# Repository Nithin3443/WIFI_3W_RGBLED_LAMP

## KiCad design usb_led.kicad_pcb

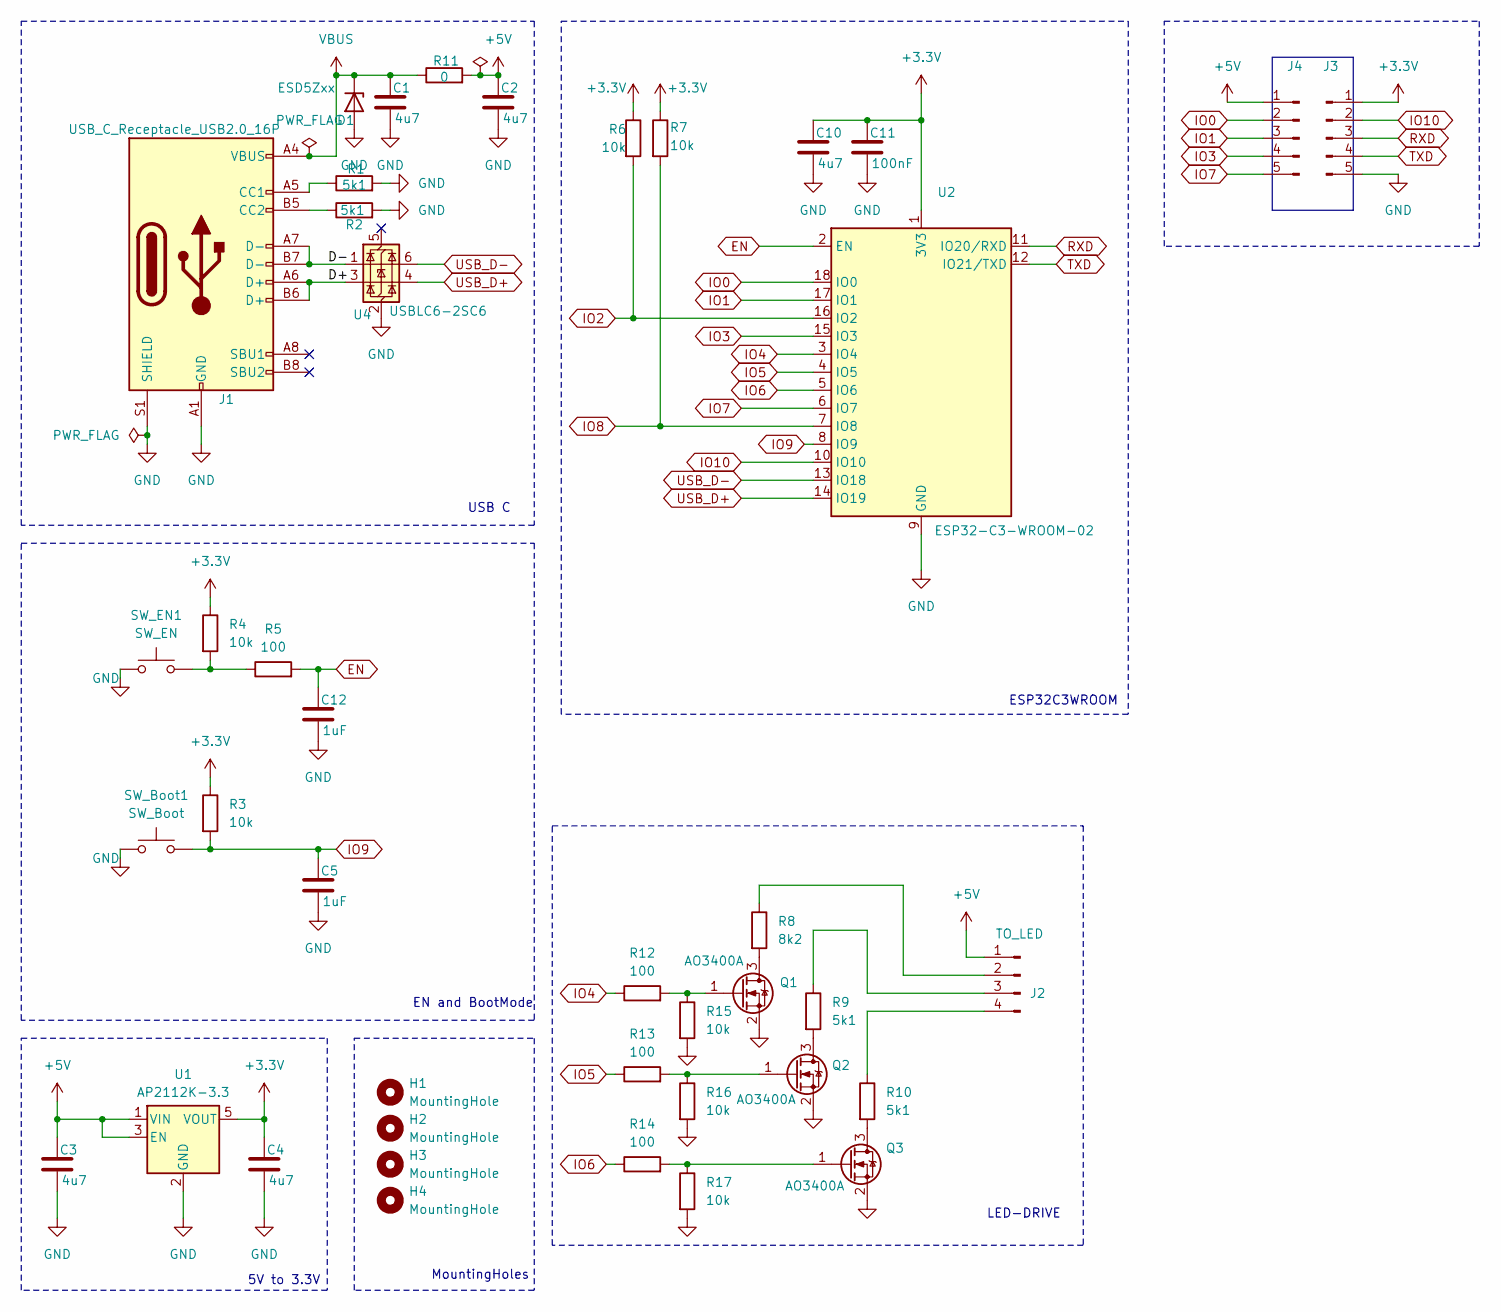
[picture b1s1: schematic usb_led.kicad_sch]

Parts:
C1, C3, C4, C10: 4u7; C_1206_3216Metric_Pad1.33x1.80mm_HandSolder
C2: 4u7; C_0805_2012Metric_Pad1.18x1.45mm_HandSolder
C5, C12: 1uF; C_0805_2012Metric_Pad1.18x1.45mm_HandSolder
C11: 100nF; C_0805_2012Metric_Pad1.18x1.45mm_HandSolder
D1: ESD5Zxx; D_SOD-523
H1, H2, H3, H4: MountingHole; MountingHole_2.2mm_M2
J1: USB_C_Receptacle_USB2.0_16P; USB_C_Receptacle_GCT_USB4105-xx-A_16P_TopMnt_Horizontal
J2: TO_LED; PinHeader_1x04_P2.54mm_Vertical
J3, J4: Conn_01x05_Pin; PinHeader_1x05_P2.54mm_Vertical
Q1, Q2, Q3: AO3400A; SOT-23W_Handsoldering
R1, R2: 5k1; R_0805_2012Metric_Pad1.20x1.40mm_HandSolder
R3, R4, R6, R7, R15, R16, R17: 10k; R_0805_2012Metric_Pad1.20x1.40mm_HandSolder
R5, R12, R13, R14: 100; R_0805_2012Metric_Pad1.20x1.40mm_HandSolder
R8: 8k2; R_2512_6332Metric_Pad1.40x3.35mm_HandSolder
R9, R10: 5k1; R_2010_5025Metric_Pad1.40x2.65mm_HandSolder
R11: 0; R_0805_2012Metric_Pad1.20x1.40mm_HandSolder
SW_Boot1: SW_Boot; SW_Push_SPST_NO_Alps_SKRK
SW_EN1: SW_EN; SW_Push_SPST_NO_Alps_SKRK
U1: AP2112K-3.3; SOT-23-5_HandSoldering
U2: ESP32-C3-WROOM-02
U4: USBLC6-2SC6; SOT-23-6

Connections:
+3.3V: C4.1, C10.1, C11.1, J3.1, R3.1, R4.1, R6.1, R7.1, U1.5 (VOUT), U2.1 (3V3)
+5V: C2.1, C3.1, J2.1, J4.1, R11.2, U1.1 (VIN), U1.3 (EN)
/D+: J1.A6 (D+), J1.B6 (D+), U4.3 (I/O2)
/D-: J1.A7 (D-), J1.B7 (D-), U4.1 (I/O1)
EN: C12.1, R5.2, U2.2 (EN)
GND: C1.2, C2.2, C3.2, C4.2, C5.2, C10.2, C11.2, C12.2, D1.2 (A), J1.A1 (GND), J1.A12 (GND), J1.B1 (GND), J1.B12 (GND), J1.S1 (SHIELD), J3.5, Q1.2 (S), Q2.2 (S), Q3.2 (S), R1.2, R2.2, R15.2, R16.2, R17.2, SW_Boot1.1, SW_EN1.1, U1.2 (GND), U2.9 (GND), U2.19 (GND), U4.2 (GND)
IO0: J4.2, U2.18 (IO0)
IO1: J4.3, U2.17 (IO1)
IO2: R6.2, U2.16 (IO2)
IO3: J4.4, U2.15 (IO3)
IO4: R12.1, U2.3 (IO4)
IO5: R13.1, U2.4 (IO5)
IO6: R14.1, U2.5 (IO6)
IO7: J4.5, U2.6 (IO7)
IO8: R7.2, U2.7 (IO8)
IO9: C5.1, R3.2, SW_Boot1.2, U2.8 (IO9)
IO10: J3.2, U2.10 (IO10)
unnamed: J1.A5 (CC1), R1.1
unnamed: J1.B5 (CC2), R2.1
unnamed: J2.2, R8.1
unnamed: J2.3, R9.1
unnamed: J2.4, R10.1
unnamed: Q1.3 (D), R8.2
unnamed: Q1.1 (G), R12.2, R15.1
unnamed: Q2.3 (D), R9.2
unnamed: Q2.1 (G), R13.2, R16.1
unnamed: Q3.3 (D), R10.2
unnamed: Q3.1 (G), R14.2, R17.1
unnamed: R4.2, R5.1, SW_EN1.2
RXD: J3.3, U2.11 (IO20/RXD)
TXD: J3.4, U2.12 (IO21/TXD)
USB_D+: U2.14 (IO19), U4.4 (I/O2)
USB_D-: U2.13 (IO18), U4.6 (I/O1)
VBUS: C1.1, D1.1 (K), J1.A4 (VBUS), J1.A9 (VBUS), J1.B4 (VBUS), J1.B9 (VBUS), R11.1

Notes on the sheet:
MountingHoles
USB C
LED-DRIVE
ESP32C3WROOM
EN and BootMode
5V to 3.3V

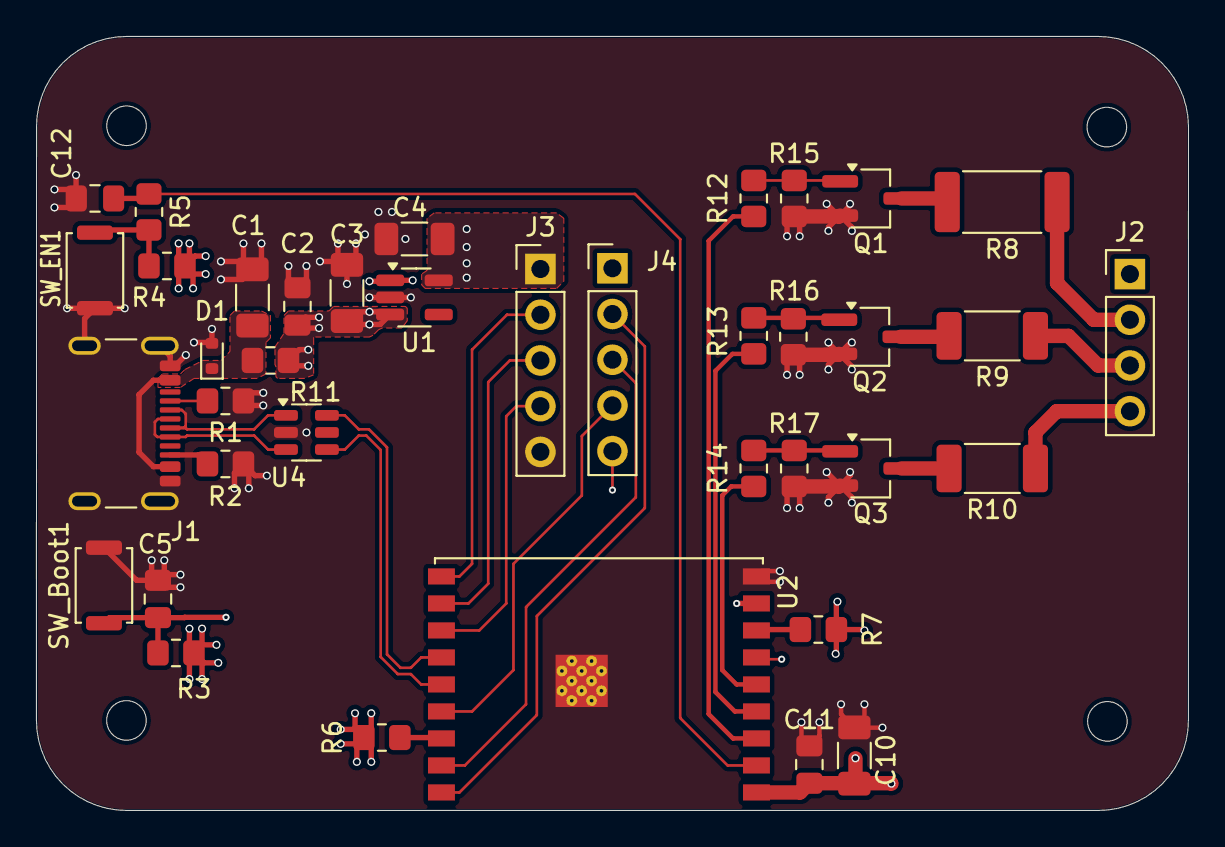
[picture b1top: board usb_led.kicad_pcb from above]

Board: 4 copper layers, 64.0 x 43.0 mm, 42 parts (0 on the bottom side), 34 nets.

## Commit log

2026-05-31 Second commit
